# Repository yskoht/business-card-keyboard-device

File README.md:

# Business Card Keyboard

## License

This software is released under the MIT License, see LICENSE.

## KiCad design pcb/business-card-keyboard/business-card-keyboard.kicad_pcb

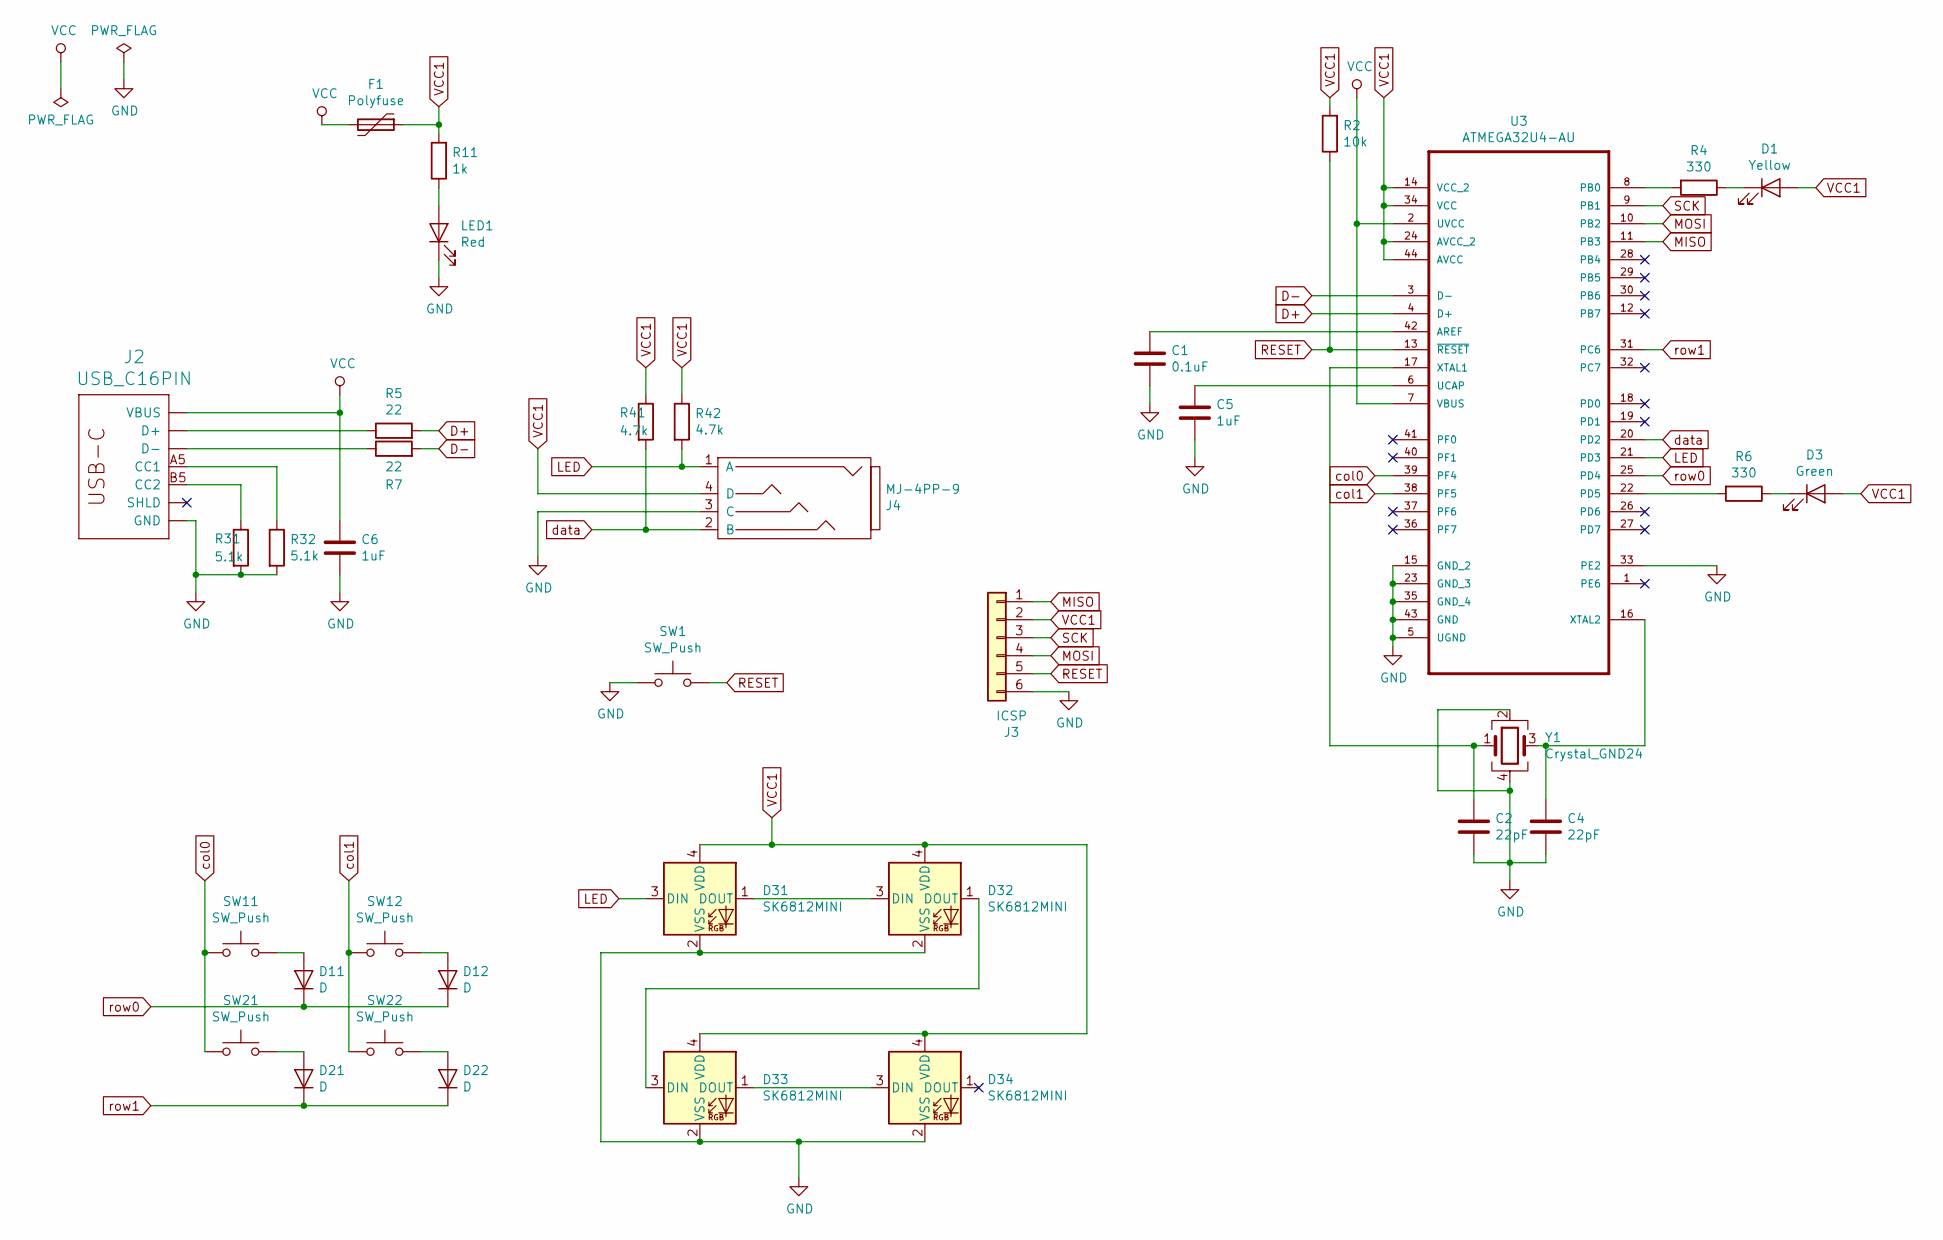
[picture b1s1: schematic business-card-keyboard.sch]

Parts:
C1: 0.1uF; C_0603_HandSoldering
C2, C4: 22pF; C_0603_HandSoldering
C5, C6: 1uF; C_0603_HandSoldering
D1: Yellow; LED_0805_HandSoldering
D3: Green; LED_0805_HandSoldering
D11, D12, D21, D22: D; D_1206
D31, D32, D33, D34: SK6812MINI
F1: Polyfuse; C_0603_HandSoldering
J2: USB_C16PIN; USB-C-COM-15111
J3: ICSP; Conn_02x03
J4: MJ-4PP-9
LED1: Red; LED_1206_HandSoldering
R2: 10k; R_1206_HandSoldering
R4, R6: 330; R_1206_HandSoldering
R5, R7: 22; R_1206_HandSoldering
R11: 1k; R_1206_HandSoldering
R31, R32: 5.1k; R_0805_HandSoldering
R41, R42: 4.7k; R_1206_HandSoldering
SW1: SW_Push; TVAF17-WFC-R
SW11, SW12, SW21, SW22: SW_Push; CPG135001S30_1.00u_PCB
U3: ATMEGA32U4-AU; ATmega32U4
Y1: Crystal_GND24; Crystal_SMD_3225-4pin_3.2x2.5mm_HandSoldering

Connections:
D+: R5.2, U3.4 (D+)
D-: R7.2, U3.3 (D-)
GND: C1.2, C2.2, C4.2, C5.2, C6.2, D31.2 (VSS), D32.2 (VSS), D33.2 (VSS), D34.2 (VSS), J2.GND, J2.GND2 (GND), J3.6, J4.3 (C), LED1.1 (K), R31.2, R32.2, SW1.1, U3.5 (UGND), U3.15 (GND_2), U3.23 (GND_3), U3.33 (PE2), U3.35 (GND_4), U3.43 (GND), Y1.2, Y1.4
LED: D31.3 (DIN), J4.1 (A), R42.2, U3.21 (PD3)
MISO: J3.1, U3.11 (PB3)
MOSI: J3.4, U3.10 (PB2)
unnamed: C1.1, U3.42 (AREF)
unnamed: C2.1, U3.17 (XTAL1), Y1.1
unnamed: C4.1, U3.16 (XTAL2), Y1.3
unnamed: C5.1, U3.6 (UCAP)
unnamed: D1.1 (K), R4.1
unnamed: D3.1 (K), R6.1
unnamed: D11.2 (A), SW11.2
unnamed: D12.2 (A), SW12.2
unnamed: D21.2 (A), SW21.2
unnamed: D22.2 (A), SW22.2
unnamed: D31.1 (DOUT), D32.3 (DIN)
unnamed: D32.1 (DOUT), D33.3 (DIN)
unnamed: D33.1 (DOUT), D34.3 (DIN)
unnamed: J2.A5 (CC1), R32.1
unnamed: J2.A6 (D+), J2.B6 (D+), R5.1
unnamed: J2.A7 (D-), J2.B7 (D-), R7.1
unnamed: J2.B5 (CC2), R31.1
unnamed: J2.SHLD1 (SHLD), J2.SHLD2 (SHLD), J2.SHLD3 (SHLD), J2.SHLD4 (SHLD), J2.SHLD5 (SHLD), J2.SHLD6 (SHLD), J2.SHLD7 (SHLD), J2.SHLD8 (SHLD)
unnamed: LED1.2 (A), R11.1
unnamed: R4.2, U3.8 (PB0)
unnamed: R6.2, U3.22 (PD5)
RESET: J3.5, R2.1, SW1.2, U3.13 (~RESET)
SCK: J3.3, U3.9 (PB1)
VCC: C6.1, F1.2, J2.VBUS1 (VBUS), J2.VBUS2 (VBUS), U3.2 (UVCC), U3.7 (VBUS)
VCC1: D1.2 (A), D3.2 (A), D31.4 (VDD), D32.4 (VDD), D33.4 (VDD), D34.4 (VDD), F1.1, J3.2, J4.4 (D), R2.2, R11.2, R41.1, R42.1, U3.14 (VCC_2), U3.24 (AVCC_2), U3.34 (VCC), U3.44 (AVCC)
col0: SW11.1, SW21.1, U3.39 (PF4)
col1: SW12.1, SW22.1, U3.38 (PF5)
data: J4.2 (B), R41.2, U3.20 (PD2)
row0: D11.1 (K), D12.1 (K), U3.25 (PD4)
row1: D21.1 (K), D22.1 (K), U3.31 (PC6)

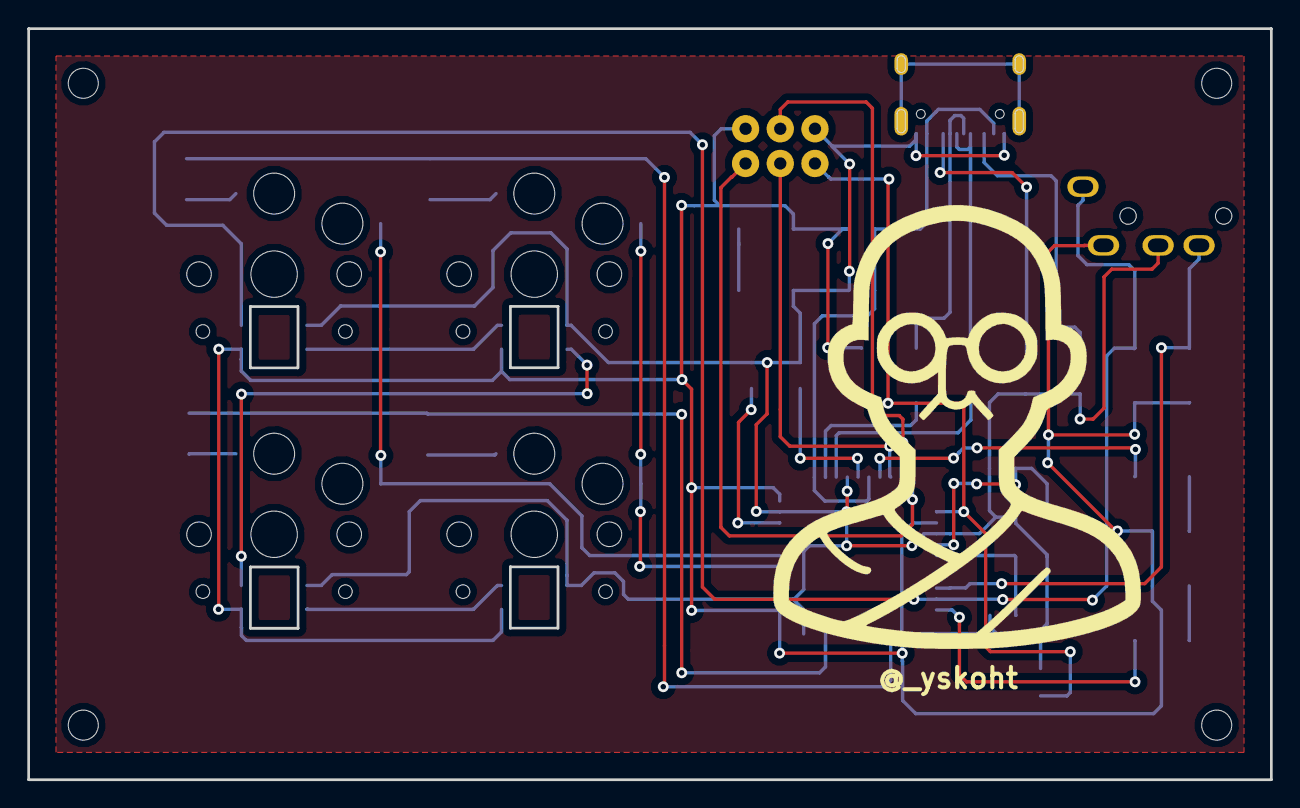
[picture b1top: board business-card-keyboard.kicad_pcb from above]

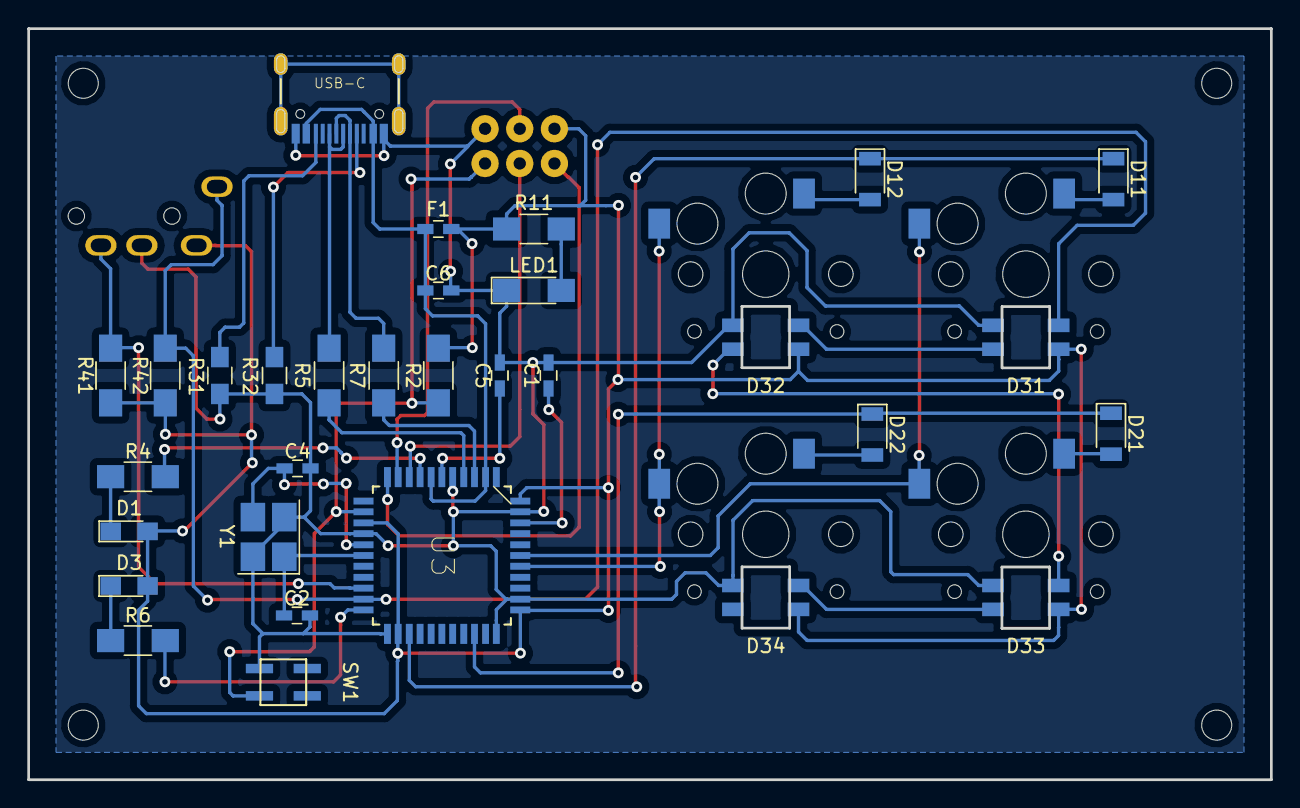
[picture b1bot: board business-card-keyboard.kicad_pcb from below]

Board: 2 copper layers, 91.0 x 55.0 mm, 37 parts (31 on the bottom side), 36 nets.

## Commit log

2019-09-26 Create LICENSE
2019-09-27 Add README.md
2019-09-27 Add images
